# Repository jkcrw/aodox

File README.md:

# AODox
Fully custom mechanical keyboard optimized for speed/ergonomics. Supports standard Qwerty and Qwerty-like key layouts as well as [Sparrowhawk steno](https://github.com/jxcrw/sphk). Powered by [QMK Firmware](https://github.com/qmk/qmk_firmware).

More documentation coming when time allows.

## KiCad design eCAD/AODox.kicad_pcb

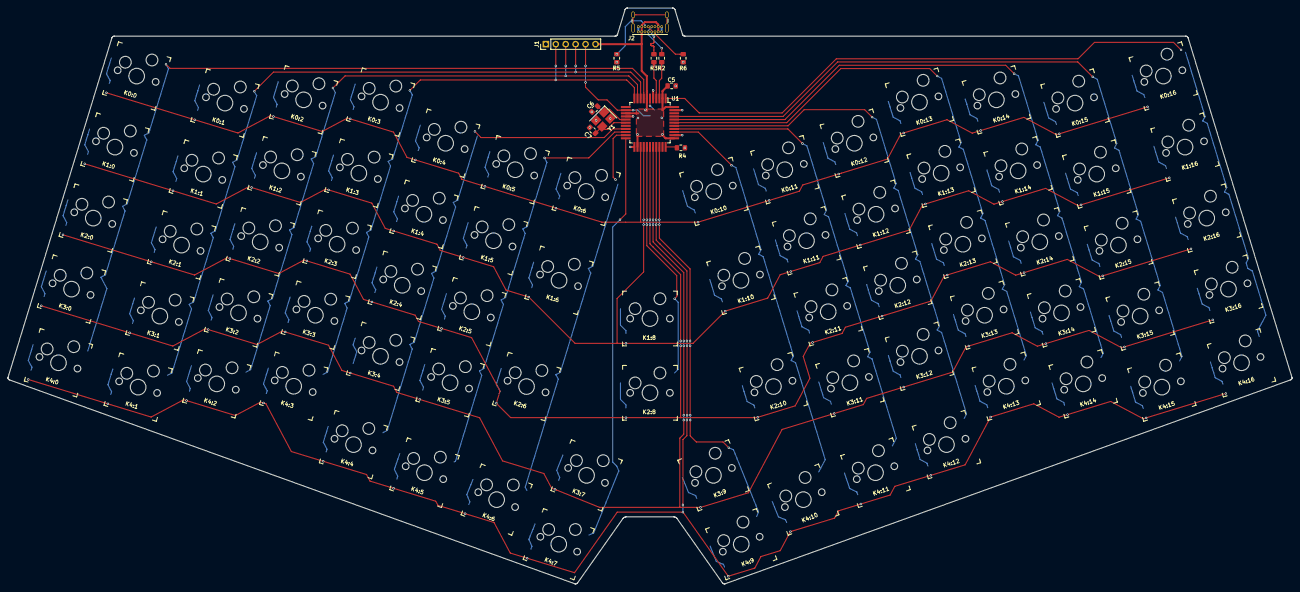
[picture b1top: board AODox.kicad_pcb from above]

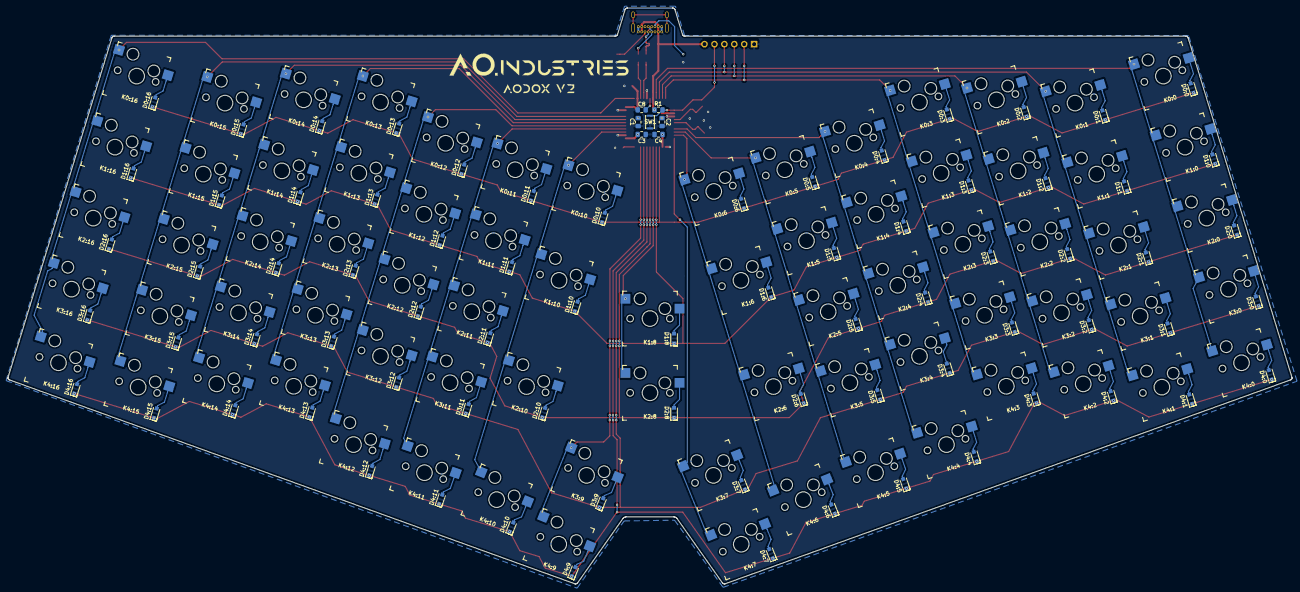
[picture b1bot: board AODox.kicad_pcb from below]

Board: 2 copper layers, 328.5 x 147.3 mm, 169 parts (82 on the bottom side), 109 nets.

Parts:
C1, C2, C3, C4: 0.1u; C_0805_2012Metric_Pad1.15x1.40mm_HandSolder
C5: 4.7u; C_0805_2012Metric_Pad1.15x1.40mm_HandSolder
C6, C7: 22p; C_0805_2012Metric_Pad1.15x1.40mm_HandSolder
C8: 1u; C_0805_2012Metric_Pad1.15x1.40mm_HandSolder
D0:0, D0:1, D0:2, D0:3, D0:4, D0:5, D0:6, D0:10, D0:11, D0:12, D0:13, D0:14, D0:15, D0:16, D1:0, D1:1, D1:2, D1:3, D1:4, D1:5, D1:6, D1:8, D1:10, D1:11, D1:12, D1:13, D1:14, D1:15, D1:16, D2:0, D2:1, D2:2, D2:3, D2:4, D2:5, D2:6, D2:8, D2:10, D2:11, D2:12, D2:13, D2:14, D2:15, D2:16, D3:0, D3:1, D3:2, D3:3, D3:4, D3:5, D3:7, D3:9, D3:11, D3:12, D3:13, D3:14, D3:15, D3:16, D4:0, D4:1, D4:2, D4:3, D4:4, D4:5, D4:6, D4:7, D4:9, D4:10, D4:11, D4:12, D4:13, D4:14, D4:15, D4:16: D_Small_ALT; D_SOD-323_HandSoldering
GRAPHIC_LOGO1: Logo; AODox_PCB_logo_Anurati
GRAPHIC_LOGO2: PCB Edge Cuts; PCB_edgecuts
J1: MCU Prog; PinHeader_1x06_P2.54mm_Vertical
J2: USB C Port; USB_C_Receptacle_GCT_USB4085
K0:0, K0:1, K0:2, K0:3, K0:4, K0:5, K0:6, K0:10, K0:11, K0:12, K0:13, K0:14, K0:15, K0:16, K1:0, K1:1, K1:2, K1:3, K1:4, K1:5, K1:6, K1:8, K1:10, K1:11, K1:12, K1:13, K1:14, K1:15, K1:16, K2:0, K2:1, K2:2, K2:3, K2:4, K2:5, K2:6, K2:8, K2:10, K2:11, K2:12, K2:13, K2:14, K2:15, K2:16, K3:0, K3:1, K3:2, K3:3, K3:4, K3:5, K3:7, K3:9, K3:11, K3:12, K3:13, K3:14, K3:15, K3:16, K4:0, K4:1, K4:2, K4:3, K4:4, K4:5, K4:6, K4:7, K4:9, K4:10, K4:11, K4:12, K4:13, K4:14, K4:15, K4:16: KEYSW; Kailh_socket
R1, R4: 10k; R_0805_2012Metric_Pad1.15x1.40mm_HandSolder
R2, R3: 22; R_0805_2012Metric_Pad1.15x1.40mm_HandSolder
R5, R6: 5.1k; R_0805_2012Metric_Pad1.15x1.40mm_HandSolder
SW1: SW_Push; SW_SPST_CK_KXT3
U1: ATMEGA32U4; TQFP-44_10x10mm_P0.8mm_HandSolder
Y1: XTAL_18p; Crystal_SMD_SeikoEpson_FA238-4Pin_3.2x2.5mm_HandSoldering

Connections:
GND: C1.2, C2.2, C3.2, C4.2, C5.2, C6.2, C7.2, C8.1, J1.1, J2.A1, J2.A12, J2.B1, J2.B12, R4.2, R5.2, R6.2, SW1.1, U1.5, U1.15, U1.23, U1.35, U1.43, Y1.2, Y1.4
unnamed: C6.1, U1.16, Y1.1
unnamed: C7.1, U1.17, Y1.3
unnamed: C8.2, U1.6
unnamed: D0:0.2, K0:0.2
unnamed: D0:1.2, K0:1.2
unnamed: D0:2.2, K0:2.2
unnamed: D0:3.2, K0:3.2
unnamed: D0:4.2, K0:4.2
unnamed: D0:5.2, K0:5.2
unnamed: D0:6.2, K0:6.2
unnamed: D0:10.2, K0:10.2
unnamed: D0:11.2, K0:11.2
unnamed: D0:12.2, K0:12.2
unnamed: D0:13.2, K0:13.2
unnamed: D0:14.2, K0:14.2
unnamed: D0:15.2, K0:15.2
unnamed: D0:16.2, K0:16.2
unnamed: D1:0.2, K1:0.2
unnamed: D1:1.2, K1:1.2
unnamed: D1:2.2, K1:2.2
unnamed: D1:3.2, K1:3.2
unnamed: D1:4.2, K1:4.2
unnamed: D1:5.2, K1:5.2
unnamed: D1:6.2, K1:6.2
unnamed: D1:8.2, K1:8.2
unnamed: D1:10.2, K1:10.2
unnamed: D1:11.2, K1:11.2
unnamed: D1:12.2, K1:12.2
unnamed: D1:13.2, K1:13.2
unnamed: D1:14.2, K1:14.2
unnamed: D1:15.2, K1:15.2
unnamed: D1:16.2, K1:16.2
unnamed: D2:0.2, K2:0.2
unnamed: D2:1.2, K2:1.2
unnamed: D2:2.2, K2:2.2
unnamed: D2:3.2, K2:3.2
unnamed: D2:4.2, K2:4.2
unnamed: D2:5.2, K2:5.2
unnamed: D2:6.2, K2:6.2
unnamed: D2:8.2, K2:8.2
unnamed: D2:10.2, K2:10.2
unnamed: D2:11.2, K2:11.2
unnamed: D2:12.2, K2:12.2
unnamed: D2:13.2, K2:13.2
unnamed: D2:14.2, K2:14.2
unnamed: D2:15.2, K2:15.2
unnamed: D2:16.2, K2:16.2
unnamed: D3:0.2, K3:0.2
unnamed: D3:1.2, K3:1.2
unnamed: D3:2.2, K3:2.2
unnamed: D3:3.2, K3:3.2
unnamed: D3:4.2, K3:4.2
unnamed: D3:5.2, K3:5.2
unnamed: D3:7.2, K3:7.2
unnamed: D3:9.2, K3:9.2
unnamed: D3:11.2, K3:11.2
unnamed: D3:12.2, K3:12.2
unnamed: D3:13.2, K3:13.2
unnamed: D3:14.2, K3:14.2
unnamed: D3:15.2, K3:15.2
unnamed: D3:16.2, K3:16.2
unnamed: D4:0.2, K4:0.2
unnamed: D4:1.2, K4:1.2
unnamed: D4:2.2, K4:2.2
unnamed: D4:3.2, K4:3.2
unnamed: D4:4.2, K4:4.2
unnamed: D4:5.2, K4:5.2
unnamed: D4:6.2, K4:6.2
unnamed: D4:7.2, K4:7.2
unnamed: D4:9.2, K4:9.2
unnamed: D4:10.2, K4:10.2
unnamed: D4:11.2, K4:11.2
unnamed: D4:12.2, K4:12.2
unnamed: D4:13.2, K4:13.2
unnamed: D4:14.2, K4:14.2
unnamed: D4:15.2, K4:15.2
unnamed: D4:16.2, K4:16.2
unnamed: J1.5, R1.2, SW1.2, U1.13
unnamed: J2.A5, R6.1
unnamed: J2.A6, J2.B6, R3.1
unnamed: J2.A7, J2.B7, R2.1
unnamed: J2.B5, R5.1
unnamed: R2.2, U1.3
unnamed: R3.2, U1.4
unnamed: R4.1, U1.33
VCC: C1.1, C2.1, C3.1, C4.1, C5.1, J1.6, J2.A4, J2.A9, J2.B4, J2.B9, R1.1, U1.2, U1.7, U1.14, U1.24, U1.34, U1.44
col0: K0:0.1, K1:0.1, K2:0.1, K3:0.1, K4:0.1, U1.8
col1: J1.4, K0:1.1, K1:1.1, K2:1.1, K3:1.1, K4:1.1, U1.9
col2: J1.3, K0:2.1, K1:2.1, K2:2.1, K3:2.1, K4:2.1, U1.10
col3: J1.2, K0:3.1, K1:3.1, K2:3.1, K3:3.1, K4:3.1, U1.11
col4: K0:4.1, K1:4.1, K2:4.1, K3:4.1, K4:4.1, U1.19
col5: K0:5.1, K1:5.1, K2:5.1, K3:5.1, K4:5.1, U1.20
col6: K0:6.1, K1:6.1, K2:6.1, K4:6.1, U1.21
col7: K3:7.1, K4:7.1, U1.22
col8: K1:8.1, K2:8.1, U1.27
col9: K3:9.1, K4:9.1, U1.31
col10: K0:10.1, K1:10.1, K2:10.1, K4:10.1, U1.36
col11: K0:11.1, K1:11.1, K2:11.1, K3:11.1, K4:11.1, U1.37
col12: K0:12.1, K1:12.1, K2:12.1, K3:12.1, K4:12.1, U1.38
col13: K0:13.1, K1:13.1, K2:13.1, K3:13.1, K4:13.1, U1.39
col14: K0:14.1, K1:14.1, K2:14.1, K3:14.1, K4:14.1, U1.40
col15: K0:15.1, K1:15.1, K2:15.1, K3:15.1, K4:15.1, U1.41
col16: K0:16.1, K1:16.1, K2:16.1, K3:16.1, K4:16.1, U1.1
row0: D0:0.1, D0:1.1, D0:2.1, D0:3.1, D0:4.1, D0:5.1, D0:6.1, D0:10.1, D0:11.1, D0:12.1, D0:13.1, D0:14.1, D0:15.1, D0:16.1, U1.25
row1: D1:0.1, D1:1.1, D1:2.1, D1:3.1, D1:4.1, D1:5.1, D1:6.1, D1:8.1, D1:10.1, D1:11.1, D1:12.1, D1:13.1, D1:14.1, D1:15.1, D1:16.1, U1.26
row2: D2:0.1, D2:1.1, D2:2.1, D2:3.1, D2:4.1, D2:5.1, D2:6.1, D2:8.1, D2:10.1, D2:11.1, D2:12.1, D2:13.1, D2:14.1, D2:15.1, D2:16.1, U1.28
row3: D3:0.1, D3:1.1, D3:2.1, D3:3.1, D3:4.1, D3:5.1, D3:7.1, D3:9.1, D3:11.1, D3:12.1, D3:13.1, D3:14.1, D3:15.1, D3:16.1, U1.29
row4: D4:0.1, D4:1.1, D4:2.1, D4:3.1, D4:4.1, D4:5.1, D4:6.1, D4:7.1, D4:9.1, D4:10.1, D4:11.1, D4:12.1, D4:13.1, D4:14.1, D4:15.1, D4:16.1, U1.30

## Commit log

2019-10-17 Take first cut at AODox layout and form factor
2019-10-21 Finish case v1
2019-10-21 Add basic MCU configuration schematic
2019-10-22 Add key matrix schematic
2019-10-22 Update schematic annotations
2019-10-22 Assign footprints to schematic symbols
2019-10-23 Create print layer for printing out and testing
2019-10-24 Update case to v2
    Remove 1.5u keys in center and moves halves closer together. Change
    interkey spacing from 0.55mm to 0.5mm. Increase base tilt from 16° to 17°.
2019-10-25 Complete v2 case design
2019-10-26 Rough out PCB layout
2019-11-21 [PCB] Route out traces on board
2019-11-24 Start versioning here at v0.2
2019-11-28 Take first steps on AODox firmware
2019-11-29 Get rough version of firmware compiling successfully
2019-11-29 Prettify layout macro and keymaps
2019-12-18 Update case design based on laser cutter testing
2020-01-12 Flesh out keymap
    Add media layer and correctly indented blank layer template.
2020-02-09 Update AODox keymap to have LCAG on left side
2020-03-03 Add rough QWTY and QSYM layers
2020-04-14 Commit before pulling in from origin
2020-06-20 Remove calc key from steno layer to prevent accidental presses
2020-09-06 Archive v0.3 files to begin development on 0.4
2021-01-24 Cosmetic reorg
2021-12-12 Several minor QOL keymap tweaks
2021-12-12 Remove unnecessary info.json file
2021-12-12 Tweak directory capitalization
    Seemed to be related to an issue that prevented the firmware from building. Seems dumb, but it really seems like that's the case.
2021-12-12 Reinclude files? Thought they were already included...
2021-12-12 Attempt to resurrect past history for AODox layout
    A nasty QMK merge conflict made it necessary to reset some repos. See `_archived\AODox keymap history.txt` for what's left of the AODox development history:
2021-12-12 Had an extra copy of some files laying around, messy messy
2021-12-12 Update directory capitalization in index
2021-12-13 Fix NKRO
2022-01-18 Commit before pulling from origin
2022-01-18 Remove erroneous stuff from merge
2022-04-17 Fix erroneous merge conflict
2022-05-10 Slightly increase tapping term
    This is to provide slightly more margin for steno chords that use mod-tap keys.
2022-06-16 Minor tweaks for 0.17.0 compatibility
2022-06-16 Start tracking new kicad files
2022-06-16 Add .gitignore
2022-11-07 Cosmetic reorg: prefer lowercase directory/file names
2022-11-07 Add personal fork of qmk_firmware as submodule
2022-11-07 Add script for copying firmware to qmk for firmware build
2022-11-07 Add README and photo
2022-11-13 docs: Add more detailed description + links
2022-11-20 todo: Righthand leader keys
2022-12-25 =all: Scrub PII + re-add files
    Everything before here is just commit messages, for historical reference.
    Scrubbed all PII.
2022-12-28 ~all: Start bringing up to date with modern qmk
    - Move keyboard metainfo from `config.h` to `info.json`.
    - Update keycodes per qmk keycode overhaul.
2023-03-20 ~keymap: Update to latest space cadet shift keycodes
2023-03-20 ~config: Remove deprecated include
2023-03-20 ~util: Update pathing in copy script
